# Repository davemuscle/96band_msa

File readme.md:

# 96 Note Music Spectrum Analyzer - FPGA

*Migrated to Git on February 20th, 2022. Updated web page on July 5th, 2020. Original release in
April 2020.*

This project converts your audio into a frequency spectrum and displays it on a VGA monitor in
real-time. The spectrum is mapped to all 96 half-notes in the first eight octaves, and is tuned to
A4 (440 Hz). It provides a visible output of 1920x1080 pixels at 60FPS, including multiple color
palette choices. There is also a choice between using an onboard microphone with auto gain control,
or a line-level input output pair.

All of the code was written in VHDL on an Artix-7. The main DSP technique used was multi-resolution,
constant-Q analysis. A custom PCB was designed at the end of project.

The general timeframe was between December 2019 and April 2020. This includes multiple rewrites of
the entire VHDL codebase, multiple hardware choice changes, and the design of the website.

## Demonstration
CTRL+click the video thumbnails to open in a new tab

| Youtube Videos |
| :--: |
| *Music Spectrum Analyzer - OSRS Harmony* |
|  |
| *Music Spectrum Analyzer - Ave Maria* |
|  |
| *Music Spectrum Analyzer - Davy Jones Theme* |
|  |

## Implementation
### Hardware Block Diagram

### Printed Circuit Board

### FPGA Design

#### Sub-designs
- I2S Master
    - Interface to I2S audio layer, reads and writes one sample of sound.
- I2S PingPong
    - Buffers up a selectable amount of audio in ping-pong fashion. Allows reading and writing
      blocks of sound to the audio layer.
- I2S Stereo2Mono
    - Converts stereo audio to mono audio
- Digital Amplifier
    - Multiplies sound data by a scalar factor based on XADC input
- Multi-Resolution Analysis
    - See below
- VGA Timing Generator
    - Creates sync signals based on screen resolution and framerate.
- VGA 2D Bin Renderer
    - Draws the frequency spectrum on the screen

### DSP Processing

The first portion of the DSP process downsamples the mono audio at 48 kHz into 8 separate octaves.
The downsampled data is buffered up, and a 256-point FFT followed by a Constant-Q transform is
performed on each octave. This downsampling and buffering is what gives us the "multi-resolution"
part of the project. The resulting frequency bins are averaged together to match the monitor's
refresh rate.

Above is the diagram for the octave bufferer. 512 samples at 48 kHz are sequentially downsampled
until we get to the loweset octave of interest.

### Reasoning behind Multi-Resolution Analysis

We actually perceive sound on a logarithmic scale, and we already are using multi-resolution
analysis! Our ears naturally have good time-localization for high-frequency sounds, and good frequency
resolution for low-frequency sounds. This means we can better determine when high-frequency sounds 
occur (time localization) and we can better distinguish between low frequency sounds (frequency resolution).

Check out the time-frequency tiling diagram:

The x-axis for each box represents a slice of time over which an FFT or some other process is
performed. The y-axis represents the frequency resolution for that time chunk.

The left diagram is how most spectrum analyzers are made -- with just an FFT. All of the tiles have
constant frequency and time resolution. 

The right is how I designed mine, attempting to match how we hear. Recording more samples allows for
a greater frequency resolution, but at the cost of higher latency. This means the lower frequencies
on the screen won't be as responsive as the higher frequencies.

The benefit to downsampling and processing multiple octaves separately is that the same sized FFT
can be used for each octave, and resources aren't wasted on the higher frequencies.

### Reasoning behind the Constant-Q Transform

Take a look at the difference in the piano keys below:

The difference between the two lowest notes on an 88-key piano is only 1.6Hz, but for the fifth
octave, the difference in the lowest notes is 26 Hz!

This is because musical notes are logarithmically spaced, just like our hearing.
Each note can be obtained from another note by multiplying by a factor of 2^(1/12).

An FFT isn't great for this, since the frequency bins are arithmetically spaced (50 Hz, 100 Hz, ...)
The Constant-Q transform IS great for this, since we can specify a geometric scale to output our
bins.

The efficient implementation of the Constant-Q transform is pretty straight forward:
Generate the kernel for the transform (a sparse matrix of    coefficients, can be done before
run-time)
Take the FFT of your data 
Apply the generated kernel (this is just a matrix-multiply)

I pasted the code for the direct form of the Constant-Q transform below. If you interested in the
efficient implementation, check out the references.

### MATLAB Code for the Constant-Q Transform (Direct-Form)
```
%input setup
fs = 4000;                         %sample rate
note = 440;                        %note frequency, A4
input = cos(2*pi*note*(0:511)/fs); %pure tone input

%fft setup
fft_output = zeros(1, length(input)); %output vector
N = length(input);                    %size

%fft direct form = dft (slow)
for k = 0:N-1
    fft_output(k+1) = input * exp(-2*pi*1i*k*(0:N-1)'/N); %complex mult + LUT
end

%cqt setup
minimum_freq = 220;                                        %two full octaves are specified between
maximum_freq = 880;                                        %the min and the max frequencies
bins_per_octave = 12;                                      %12 bins per octave = 1 bin for 1 note
Q = 1/(2^(1/bins_per_octave)-1);                           %Q factor of the filterbank
K = ceil(bins_per_octave*log2(maximum_freq/minimum_freq)); %total num bins
cqt_output = zeros(1,K);

%cqt direct form
%this is the slow way to calculate the cqt
for k = 1:K
   N = round(Q*fs/(minimum_freq*2^((k-1)/bins_per_octave)));    %variable length
   cqt_output(k) = cqt_input(1:N) * exp(-2*pi*1i*Q*(0:N-1)'/N); %same form as fft
end

%plots of obtained data obtained
close all;
figure %only plotting one image of the spectrum
stem(abs(fft_output(1:length(input)/2)))
title('fft output');
ylabel('magnitude');
xlabel('bin');
figure
stem(abs(cqt_output))
title('cqt output');
ylabel('magnitude');
xlabel('bin');
```

### References
1. [Piano Key Frequencies](https://en.wikipedia.org/wiki/Piano_key_frequencies)
2. [Benjamin Blankertz, Constant-Q Transform](http://doc.ml.tu-berlin.de/bbci/material/publications/Bla_constQ.pdf)
3. [Brown & Puckette , Effecient Constant-Q Transform](http://academics.wellesley.edu/Physics/brown/pubs/effalgV92P2698-P2701.pdf)
4. [Djikstra's Square Root Algorithm](http://lib.tkk.fi/Diss/2005/isbn9512275279/article3.pdf)
5. [VGA Timing](https://projectf.io/posts/video-timings-vga-720p-1080p/)
6. [Artix 7 Board](https://digilent.com/shop/cmod-a7-breadboardable-artix-7-fpga-module/)
7. [Website Inspiration, 96khz.org](http://www.96khz.org/projects.htm)

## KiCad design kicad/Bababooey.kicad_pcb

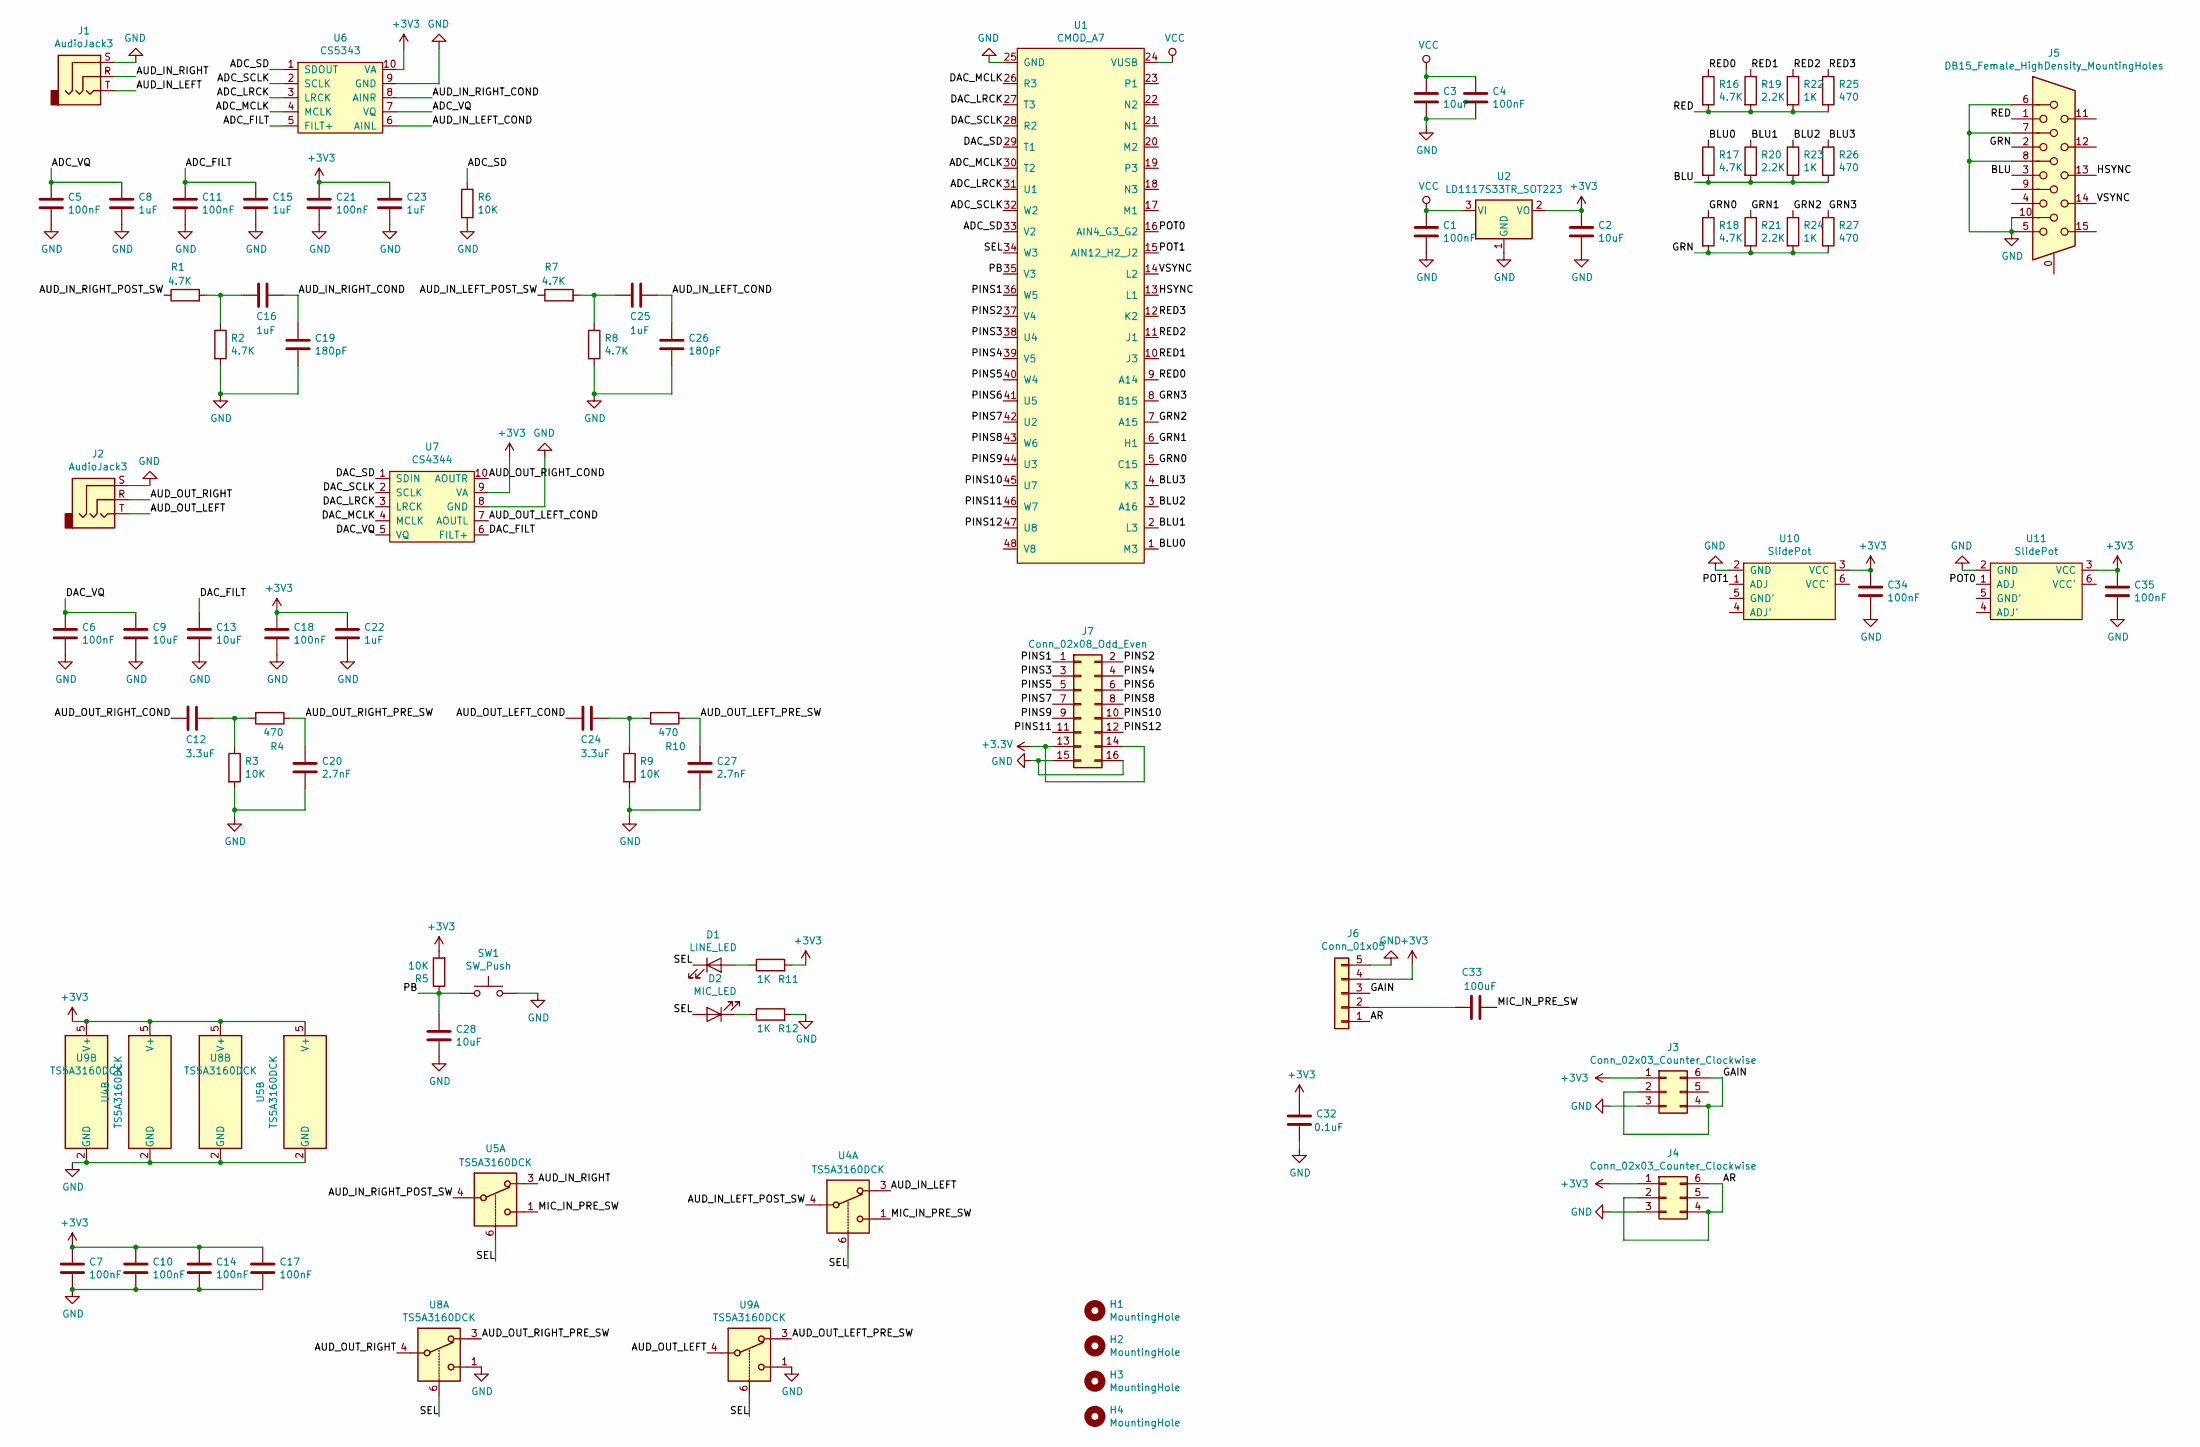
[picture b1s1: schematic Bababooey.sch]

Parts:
C1, C4, C5, C6, C7, C10, C11, C14, C17, C18, C21, C34, C35: 100nF; C_1210_3225Metric_Pad1.42x2.65mm_HandSolder
C2, C3, C9, C13, C28: 10uF; C_1210_3225Metric_Pad1.42x2.65mm_HandSolder
C8, C15, C16, C22, C23, C25: 1uF; C_1210_3225Metric_Pad1.42x2.65mm_HandSolder
C12, C24: 3.3uF; C_1210_3225Metric_Pad1.42x2.65mm_HandSolder
C19, C26: 180pF; C_1210_3225Metric_Pad1.42x2.65mm_HandSolder
C20, C27: 2.7nF; C_1210_3225Metric_Pad1.42x2.65mm_HandSolder
C32: 0.1uF; C_1210_3225Metric_Pad1.42x2.65mm_HandSolder
C33: 100uF; C_1210_3225Metric_Pad1.42x2.65mm_HandSolder
D1: LINE_LED; LED_1210_3225Metric_Pad1.42x2.65mm_HandSolder
D2: MIC_LED; LED_1210_3225Metric_Pad1.42x2.65mm_HandSolder
H1, H2, H3, H4: MountingHole; MountingHole_3.5mm
J1, J2: AudioJack3; Jack_3.5mm_CUI_SJ-3524-SMT_Horizontal
J3, J4: Conn_02x03_Counter_Clockwise; PinHeader_2x03_P2.54mm_Vertical
J5: DB15_Female_HighDensity_MountingHoles; DSUB-15-HD_Female_Horizontal_P2.29x1.98mm_EdgePinOffset8.35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
J6: Conn_01x05; PinSocket_1x05_P2.54mm_Vertical
J7: Conn_02x08_Odd_Even; PinSocket_2x08_P2.54mm_Vertical
R1, R2, R7, R8, R16, R17, R18: 4.7K; R_1210_3225Metric_Pad1.42x2.65mm_HandSolder
R3, R5, R6, R9: 10K; R_1210_3225Metric_Pad1.42x2.65mm_HandSolder
R4, R10, R25, R26, R27: 470; R_1210_3225Metric_Pad1.42x2.65mm_HandSolder
R11, R12, R22, R23, R24: 1K; R_1210_3225Metric_Pad1.42x2.65mm_HandSolder
R19, R20, R21: 2.2K; R_1210_3225Metric_Pad1.42x2.65mm_HandSolder
SW1: SW_Push; SW_SPST_TL3305B
U1: CMOD_A7
U2: LD1117S33TR_SOT223; SOT-223-3_TabPin2
U4, U5, U8, U9: TS5A3160DCK; SOT-363_SC-70-6
U6: CS5343; TSSOP-10_3x3mm_P0.5mm
U7: CS4344; TSSOP-10_3x3mm_P0.5mm
U10, U11: SlidePot

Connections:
/ADC_FILT: C11.1, C15.1, U6.5 (FILT+)
/ADC_LRCK: U1.31 (U1), U6.3 (LRCK)
/ADC_MCLK: U1.30 (T2), U6.4 (MCLK)
/ADC_SCLK: U1.32 (W2), U6.2 (SCLK)
/ADC_SD: R6.1, U1.33 (V2), U6.1 (SDOUT)
/ADC_VQ: C5.1, C8.1, U6.7 (VQ)
/AR: J4.2, J4.4, J4.6, J6.1
/AUD_IN_LEFT: J1.T, U4.3
/AUD_IN_LEFT_COND: C25.1, C26.1, U6.6 (AINL)
/AUD_IN_LEFT_POST_SW: R7.1, U4.4
/AUD_IN_RIGHT: J1.R, U5.3
/AUD_IN_RIGHT_COND: C16.1, C19.1, U6.8 (AINR)
/AUD_IN_RIGHT_POST_SW: R1.1, U5.4
/AUD_OUT_LEFT: J2.T, U9.4
/AUD_OUT_LEFT_COND: C24.2, U7.7 (AOUTL)
/AUD_OUT_LEFT_PRE_SW: C27.1, R10.1, U9.3
/AUD_OUT_RIGHT: J2.R, U8.4
/AUD_OUT_RIGHT_COND: C12.2, U7.10 (AOUTR)
/AUD_OUT_RIGHT_PRE_SW: C20.1, R4.1, U8.3
/BLU: J5.3, R17.2, R20.2, R23.2, R26.2
/BLU0: R17.1, U1.1 (M3)
/BLU1: R20.1, U1.2 (L3)
/BLU2: R23.1, U1.3 (A16)
/BLU3: R26.1, U1.4 (K3)
/DAC_FILT: C13.1, U7.6 (FILT+)
/DAC_LRCK: U1.27 (T3), U7.3 (LRCK)
/DAC_MCLK: U1.26 (R3), U7.4 (MCLK)
/DAC_SCLK: U1.28 (R2), U7.2 (SCLK)
/DAC_SD: U1.29 (T1), U7.1 (SDIN)
/DAC_VQ: C6.1, C9.1, U7.5 (VQ)
/GAIN: J3.2, J3.4, J3.6, J6.3
/GRN: J5.2, R18.2, R21.2, R24.2, R27.2
/GRN0: R18.1, U1.5 (C15)
/GRN1: R21.1, U1.6 (H1)
/GRN2: R24.1, U1.7 (A15)
/GRN3: R27.1, U1.8 (B15)
/HSYNC: J5.13, U1.13 (L1)
/MIC_IN_PRE_SW: C33.2, U4.1, U5.1
/PB: C28.1, R5.1, SW1.1, U1.35 (V3)
/PINS1: J7.1, U1.36 (W5)
/PINS2: J7.2, U1.37 (V4)
/PINS3: J7.3, U1.38 (U4)
/PINS4: J7.4, U1.39 (V5)
/PINS5: J7.5, U1.40 (W4)
/PINS6: J7.6, U1.41 (U5)
/PINS7: J7.7, U1.42 (U2)
/PINS8: J7.8, U1.43 (W6)
/PINS9: J7.9, U1.44 (U3)
/PINS10: J7.10, U1.45 (U7)
/PINS11: J7.11, U1.46 (W7)
/PINS12: J7.12, U1.47 (U8)
/POT0: U1.16 (AIN4_G3_G2), U11.1 (ADJ)
/POT1: U1.15 (AIN12_H2_J2), U10.1 (ADJ)
/RED: J5.1, R16.2, R19.2, R22.2, R25.2
/RED0: R16.1, U1.9 (A14)
/RED1: R19.1, U1.10 (J3)
/RED2: R22.1, U1.11 (J1)
/RED3: R25.1, U1.12 (K2)
/SEL: D1.1 (K), D2.2 (A), U1.34 (W3), U4.6, U5.6, U8.6, U9.6
/VSYNC: J5.14, U1.14 (L2)
GND: C1.2, C2.2, C3.2, C4.2, C5.2, C6.2, C7.2, C8.2, C9.2, C10.2, C11.2, C13.2, C14.2, C15.2, C17.2, C18.2, C19.2, C20.2, C21.2, C22.2, C23.2, C26.2, C27.2, C28.2, C32.2, C34.2, C35.2, J1.S, J2.S, J3.3, J4.3, J5.5, J5.6, J5.7, J5.8, J5.10, J6.5, J7.15, J7.16, R2.2, R3.2, R6.2, R8.2, R9.2, R12.2, SW1.2, U1.25 (GND), U2.1 (GND), U4.2 (GND), U5.2 (GND), U6.9 (GND), U7.8 (GND), U8.1, U8.2 (GND), U9.1, U9.2 (GND), U10.2 (GND), U11.2 (GND)
unnamed: C12.1, R3.1, R4.2
unnamed: C16.2, R1.2, R2.1
unnamed: C24.1, R9.1, R10.2
unnamed: C25.2, R7.2, R8.1
unnamed: C33.1, J6.2
unnamed: D1.2 (A), R11.1
unnamed: D2.1 (K), R12.1
VCC: C1.1, C3.1, C4.1, U1.24 (VUSB), U2.3 (VI)

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
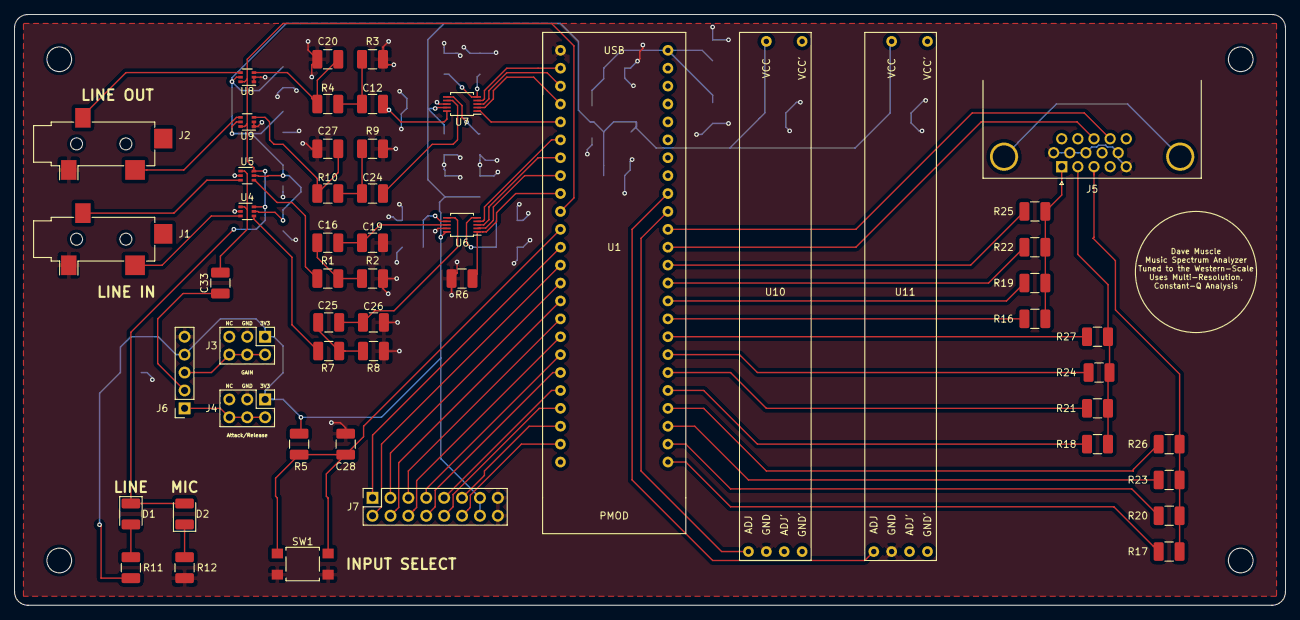
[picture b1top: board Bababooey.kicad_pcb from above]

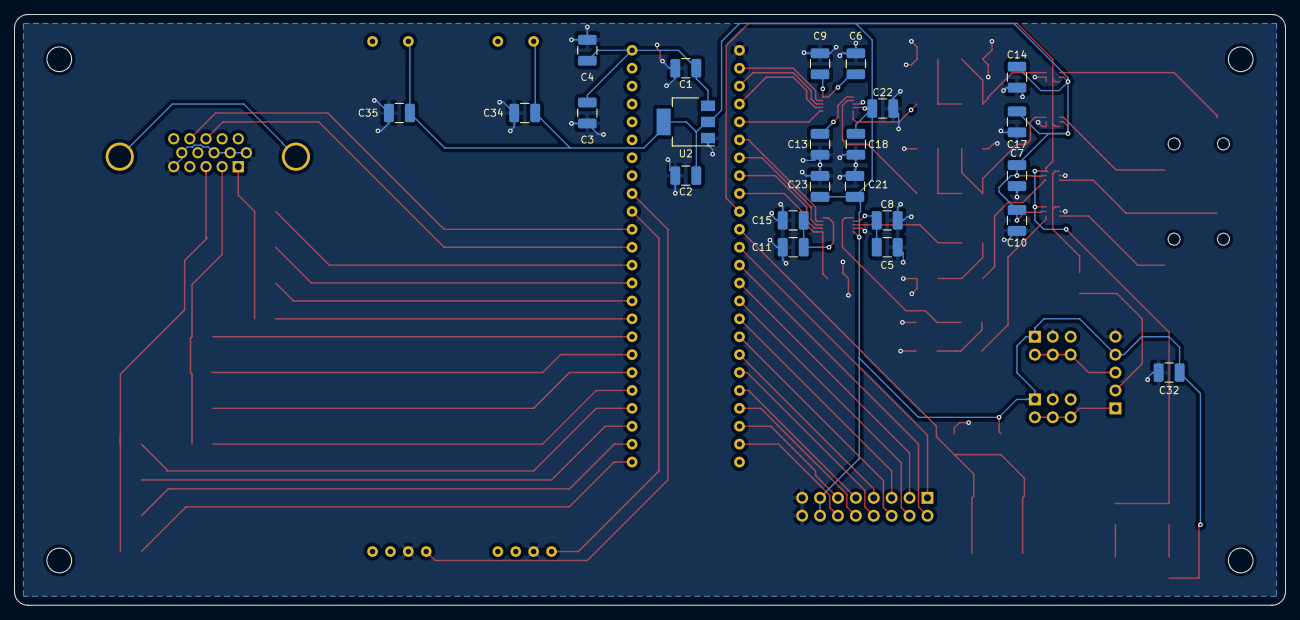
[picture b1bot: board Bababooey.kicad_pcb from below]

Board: 2 copper layers, 180.3 x 83.8 mm, 80 parts (23 on the bottom side), 70 nets.

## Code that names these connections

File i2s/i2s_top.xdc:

set_property PACKAGE_PIN T3 [get_ports dac_lrclk]
set_property PACKAGE_PIN R3 [get_ports dac_mclk]
set_property PACKAGE_PIN R2 [get_ports dac_sclk]
set_property PACKAGE_PIN T2 [get_ports adc_mclk]
set_property PACKAGE_PIN U1 [get_ports adc_lrclk]
set_property PACKAGE_PIN W2 [get_ports adc_sclk]
set_property PACKAGE_PIN T1 [get_ports sdout]
set_property PACKAGE_PIN V2 [get_ports sdin]
set_property IOSTANDARD LVCMOS33 [get_ports sdout]
set_property IOSTANDARD LVCMOS33 [get_ports sdin]
set_property IOSTANDARD LVCMOS33 [get_ports dac_sclk]
set_property IOSTANDARD LVCMOS33 [get_ports dac_mclk]
set_property IOSTANDARD LVCMOS33 [get_ports dac_lrclk]
set_property IOSTANDARD LVCMOS33 [get_ports adc_sclk]
set_property IOSTANDARD LVCMOS33 [get_ports adc_mclk]
set_property IOSTANDARD LVCMOS33 [get_ports adc_lrclk]

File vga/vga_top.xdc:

#PIO01 -- bottom right pin
set_property PACKAGE_PIN L2 [get_ports vsync]
set_property IOSTANDARD LVCMOS33 [get_ports vsync]

#PIO02
set_property PACKAGE_PIN L1 [get_ports hsync]
set_property IOSTANDARD LVCMOS33 [get_ports hsync]


set_property PACKAGE_PIN K3 [get_ports {blu[3]}]
set_property PACKAGE_PIN A16 [get_ports {blu[2]}]
set_property PACKAGE_PIN L3  [get_ports {blu[1]}]
set_property PACKAGE_PIN M3  [get_ports {blu[0]}]
set_property IOSTANDARD LVCMOS33 [get_ports {blu[*]}]

set_property PACKAGE_PIN B15  [get_ports {grn[3]}]
set_property PACKAGE_PIN A15  [get_ports {grn[2]}]
set_property PACKAGE_PIN H1  [get_ports {grn[1]}]
set_property PACKAGE_PIN C15  [get_ports {grn[0]}]
set_property IOSTANDARD LVCMOS33 [get_ports {grn[*]}]

set_property PACKAGE_PIN K2  [get_ports {red[3]}]
set_property PACKAGE_PIN J1  [get_ports {red[2]}] 
set_property PACKAGE_PIN J3  [get_ports {red[1]}]
set_property PACKAGE_PIN A14  [get_ports {red[0]}]
set_property IOSTANDARD LVCMOS33 [get_ports {red[*]}]

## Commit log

2022-02-20 readme.md
2022-02-20 moved code from windows to github
2022-02-20 added pcb files
2022-02-20 moved xilinx ip into separate tarball
2022-02-20 update readme 1
2022-02-20 update readme 2
2022-02-20 update readme 3
2022-02-20 update readme 4
2022-02-20 update readme 5
2022-02-20 update readme 6
2022-02-20 update readme 7
2022-02-20 update readme 8
2022-02-20 update readme 9
